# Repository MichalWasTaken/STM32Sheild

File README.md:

Shield for STM32 nucleo board to test nitrox analyzer project.

Components to be on the sield:
- Connectors
- Amplifier
- Button
- Potmeter
- Optional:
- Power elements (batt charger, buck-boost modules)

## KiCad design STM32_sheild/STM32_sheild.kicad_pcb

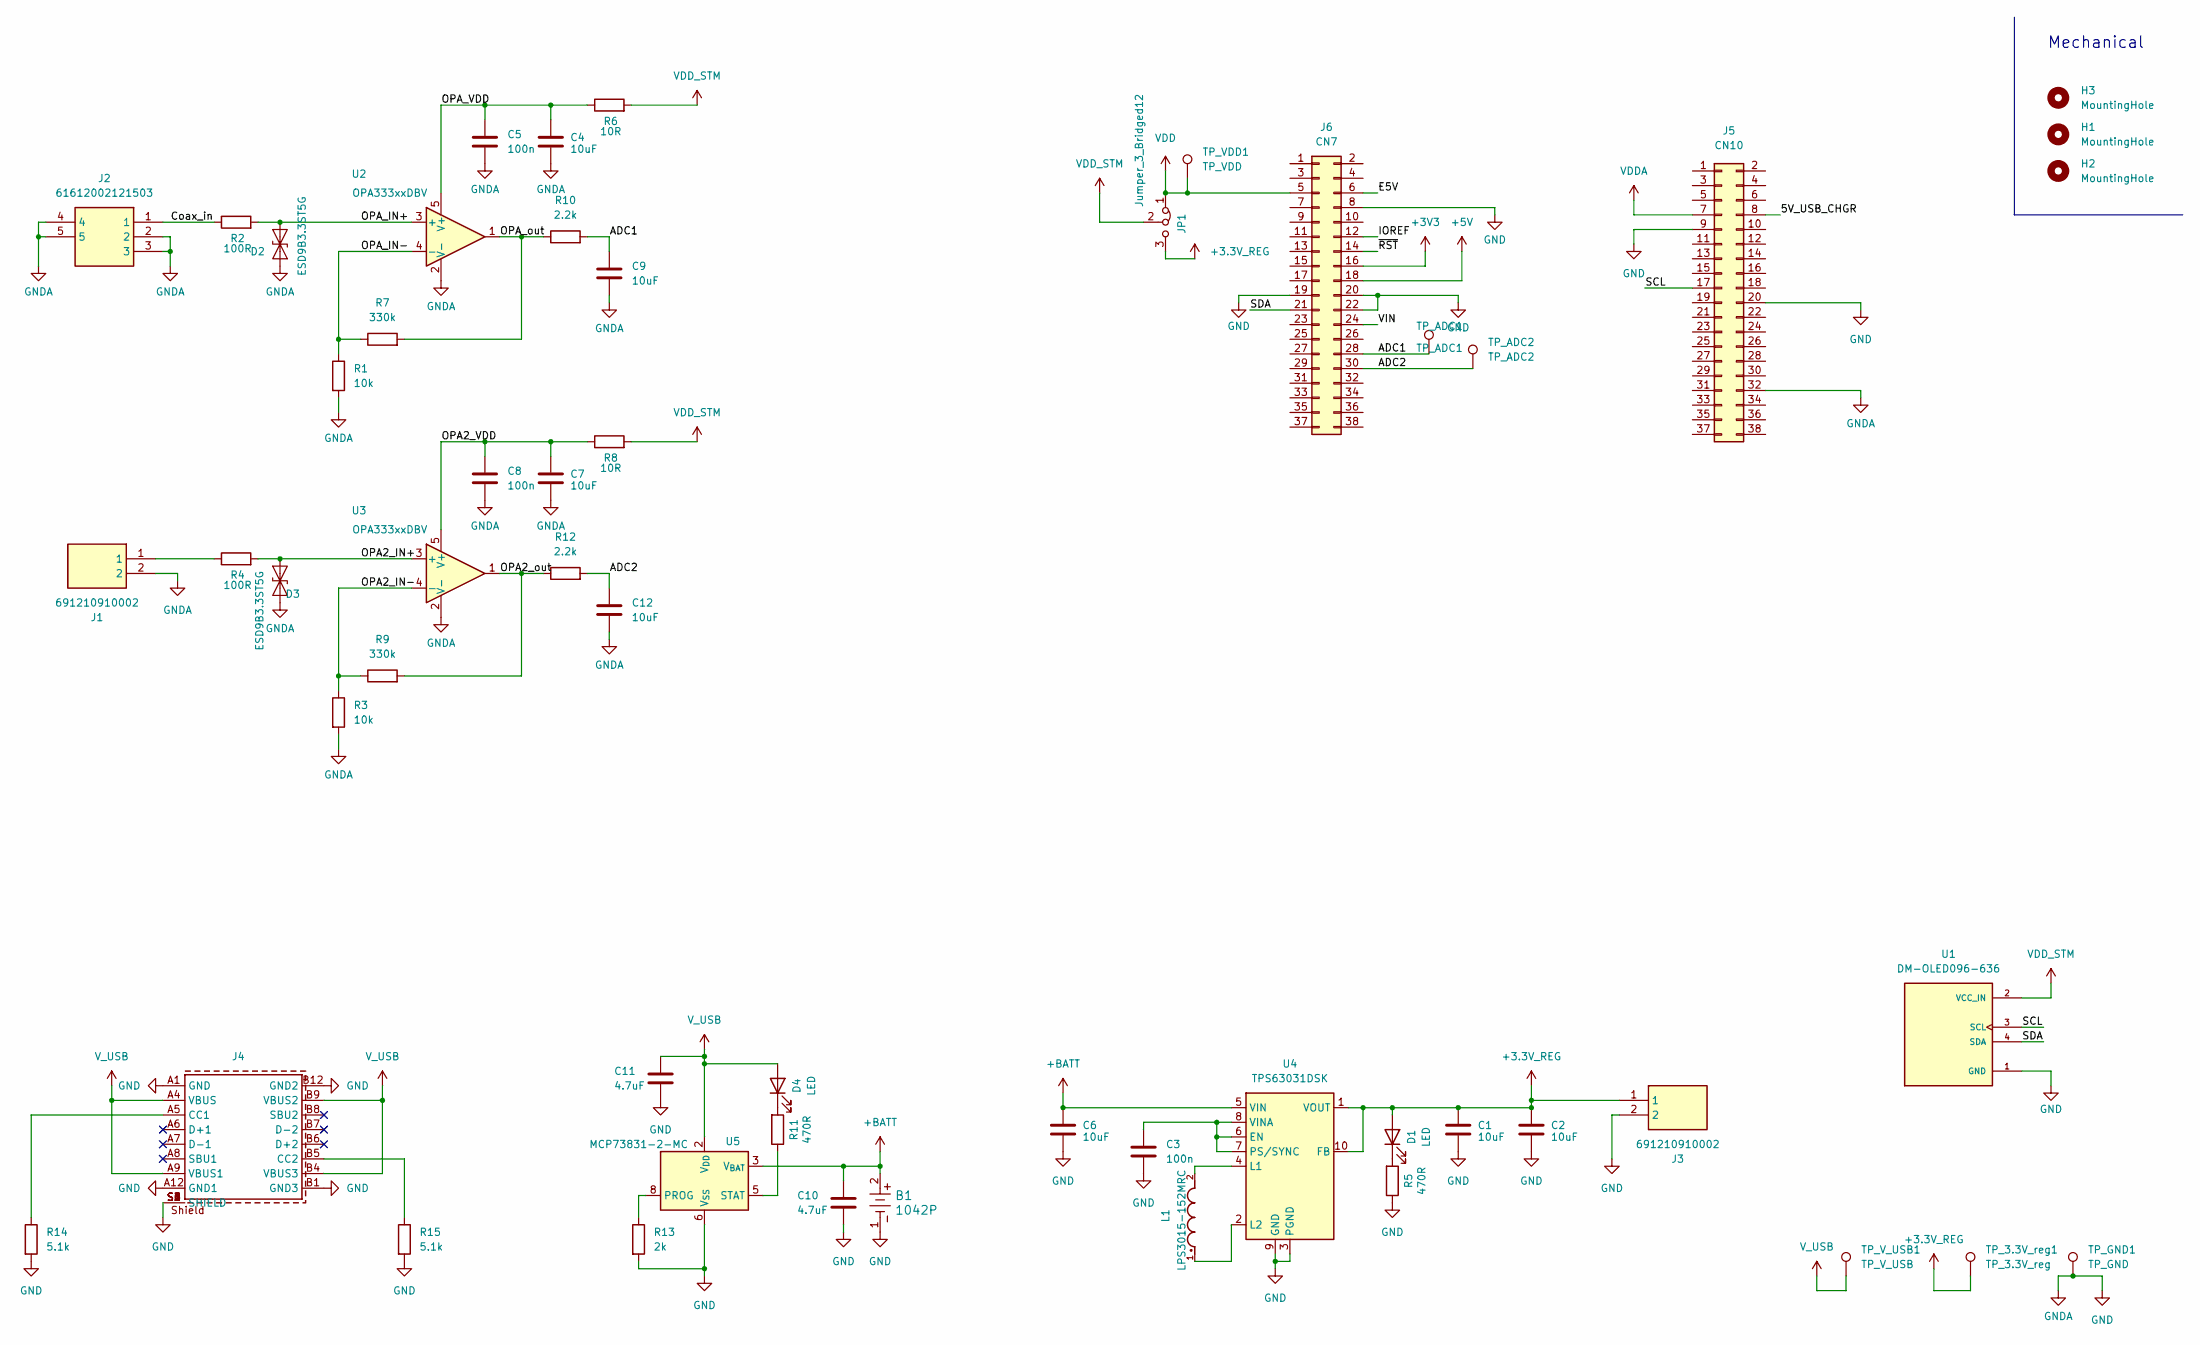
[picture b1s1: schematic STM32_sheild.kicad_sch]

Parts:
B1: 1042P; 1042P_KEY
C1, C2, C4, C6, C7, C9, C12: 10uF; C_0805_2012Metric
C3, C5, C8: 100n; C_0805_2012Metric
C10, C11: 4.7uF; C_0805_2012Metric
D1, D4: LED; LED_0805_2012Metric
D2, D3: ESD9B3.3ST5G; D_SOD-923
H1, H2, H3: MountingHole; MountingHole_3.2mm_M3
J1, J3: 691210910002; Mouser Part Number 710-691210910002
J2: 61612002121503; Mouser Part Number 710-61612002121503
J4: 629722010114; J_Wurth_WR-USB_629722050114; Working Voltage (V (DC)) 48 V (DC); Part Number 629722010114
J5: CN10; PinSocket_2x19_P2.54mm_Vertical
J6: CN7; PinSocket_2x19_P2.54mm_Vertical
JP1: Jumper_3_Bridged12; SolderJumper-3_P1.3mm_Bridged2Bar12_Pad1.0x1.5mm
L1: LPS3015-152MRC; IND_LPS3015-152MRC; PARTREV 12/13/21
R1, R3: 10k; R_0805_2012Metric
R2, R4: 100R; R_0805_2012Metric
R5, R11: 470R; R_0805_2012Metric
R6, R8: 10R; R_0805_2012Metric
R7, R9: 330k; R_0805_2012Metric
R10, R12: 2.2k; R_0805_2012Metric
R13: 2k; R_0805_2012Metric
R14, R15: 5.1k; R_0805_2012Metric
TP_3.3V_reg1: TP_3.3V_reg; TestPoint_Keystone_5010-5014_Multipurpose
TP_ADC1: TP_ADC1; TestPoint_Keystone_5010-5014_Multipurpose
TP_ADC2: TP_ADC2; TestPoint_Keystone_5010-5014_Multipurpose
TP_GND1: TP_GND; TestPoint_Keystone_5010-5014_Multipurpose
TP_VDD1: TP_VDD; TestPoint_Keystone_5010-5014_Multipurpose
TP_V_USB1: TP_V_USB; TestPoint_Keystone_5010-5014_Multipurpose
U1: DM-OLED096-636; MODULE_DM-OLED096-636; PARTREV 2018-09-10
U2, U3: OPA333xxDBV; SOT-23-5
U4: TPS63031DSK; WSON-10-1EP_2.5x2.5mm_P0.5mm_EP1.2x2mm
U5: MCP73831-2-MC; DFN-8-1EP_3x2mm_P0.5mm_EP1.7x1.4mm

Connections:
+3.3V_REG: C1.1, C2.1, D1.2 (A), J3.1, JP1.3 (B), TP_3.3V_reg1.1 (1_1), U4.1 (VOUT), U4.10 (FB)
+3V3: J6.16
+5V: J6.18
+BATT: B1.2, C6.1, C10.1, U4.5 (VIN), U5.3 (V_{BAT}), U5.4 (V_{BAT})
/5V_USB_CHGR: J5.8
/ADC1: C9.1, J6.28, R10.2, TP_ADC1.1 (1_1)
/ADC2: C12.1, J6.30, R12.2, TP_ADC2.1 (1_1)
/Coax_in: J2.1, R2.1
/E5V: J6.6
/IOREF: J6.12
/OPA2_IN+: D3.2 (A2), R4.2, U3.3 (+)
/OPA2_IN-: R3.1, R9.1, U3.4 (-)
/OPA2_VDD: C7.1, C8.1, R8.1, U3.5 (V+)
/OPA2_out: R9.2, R12.1, U3.1
/OPA_IN+: D2.2 (A2), R2.2, U2.3 (+)
/OPA_IN-: R1.1, R7.1, U2.4 (-)
/OPA_VDD: C4.1, C5.1, R6.1, U2.5 (V+)
/OPA_out: R7.2, R10.1, U2.1
/SCL: J5.17, U1.3 (SCL)
/SDA: J6.21, U1.4 (SDA)
/VIN: J6.24
/~RST: J6.14
GND: B1.1, C1.2, C2.2, C3.2, C4.2, C5.2, C6.2, C7.2, C8.2, C9.2, C10.2, C11.2, C12.2, D2.1 (A1), D3.1 (A1), J1.2, J2.2, J2.3, J2.4, J2.5, J3.2, J4.A1 (GND), J4.A12 (GND1), J4.B1 (GND3), J4.B12 (GND2), J4.S1 (SHIELD), J4.S2 (SHIELD), J4.S3 (SHIELD), J4.S4 (SHIELD), J4.S5 (SHIELD), J4.S6 (SHIELD), J5.9, J5.20, J5.32, J6.8, J6.19, J6.20, J6.22, R1.2, R3.2, R5.1, R13.2, R14.2, R15.2, TP_GND1.1 (1_1), U1.1 (GND), U2.2 (V-), U3.2 (V-), U4.3 (PGND), U4.9 (GND), U4.11 (PGND), U5.6 (V_{SS})
unnamed: D1.1 (K), R5.2
unnamed: D4.1 (K), R11.2
unnamed: J1.1, R4.1
unnamed: J4.A5 (CC1), R14.1
unnamed: J4.B5 (CC2), R15.1
unnamed: C3.1, U4.6 (EN), U4.7 (PS/SYNC), U4.8 (VINA)
unnamed: L1.2, U4.4 (L1)
unnamed: L1.1, U4.2 (L2)
unnamed: R13.1, U5.8 (PROG)
unnamed: R11.1, U5.5 (STAT)
VDD: J6.5, JP1.1 (A), TP_VDD1.1 (1_1)
VDDA: J5.7
VDD_STM: JP1.2 (C), R6.2, R8.2, U1.2 (VCC_IN)
V_USB: C11.1, D4.2 (A), J4.A4 (VBUS), J4.A9 (VBUS1), J4.B4 (VBUS3), J4.B9 (VBUS2), TP_V_USB1.1 (1_1), U5.1 (V_{DD}), U5.2 (V_{DD})

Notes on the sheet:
Mechanical

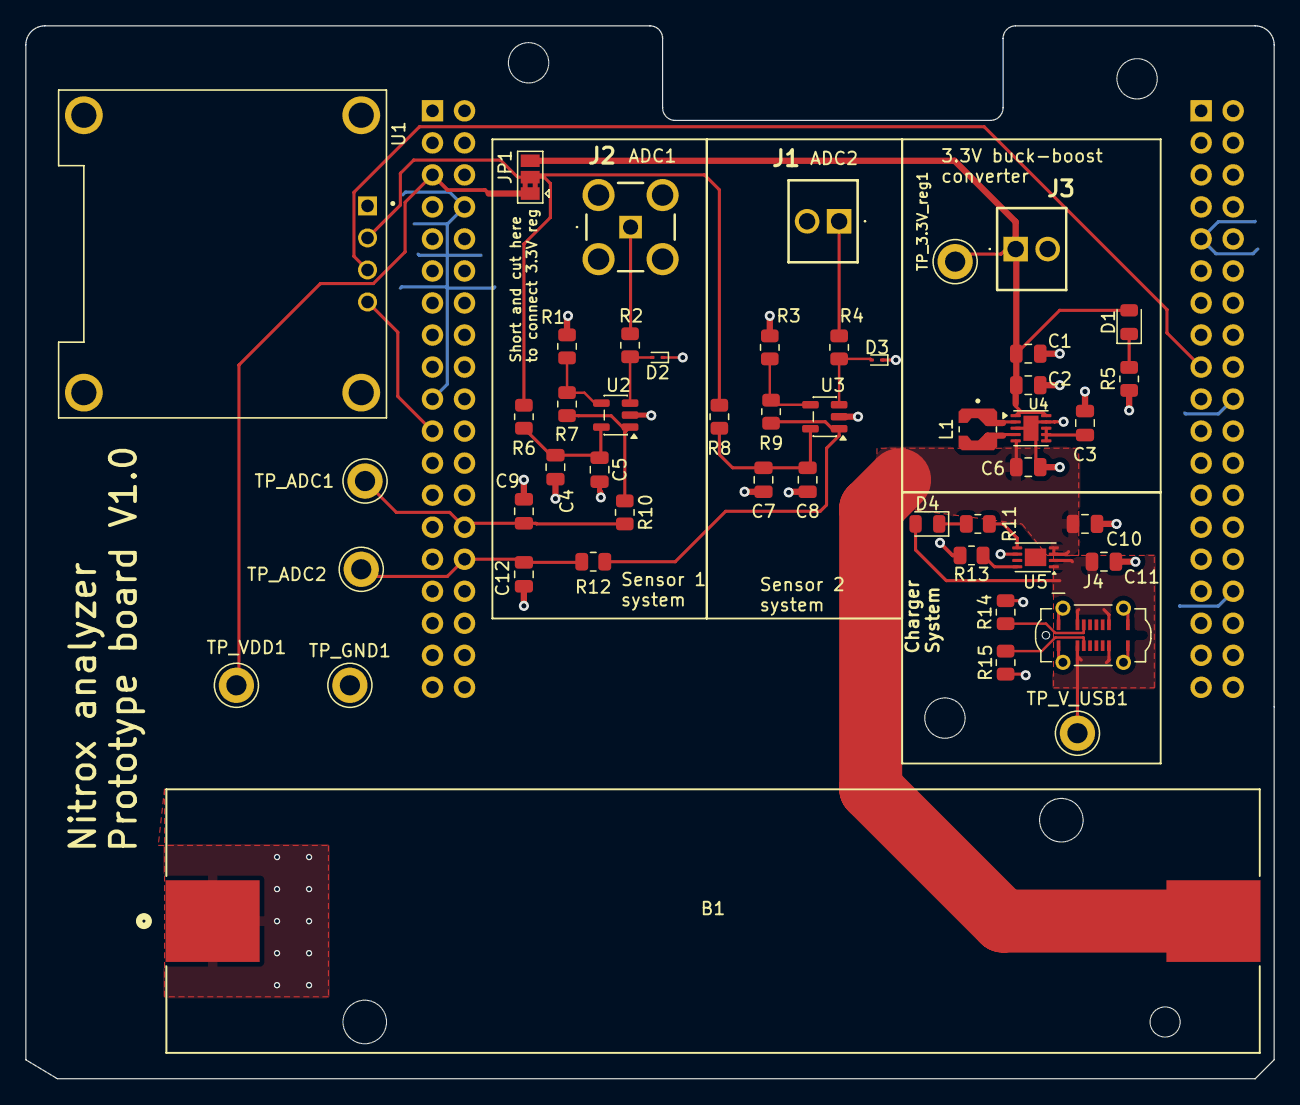
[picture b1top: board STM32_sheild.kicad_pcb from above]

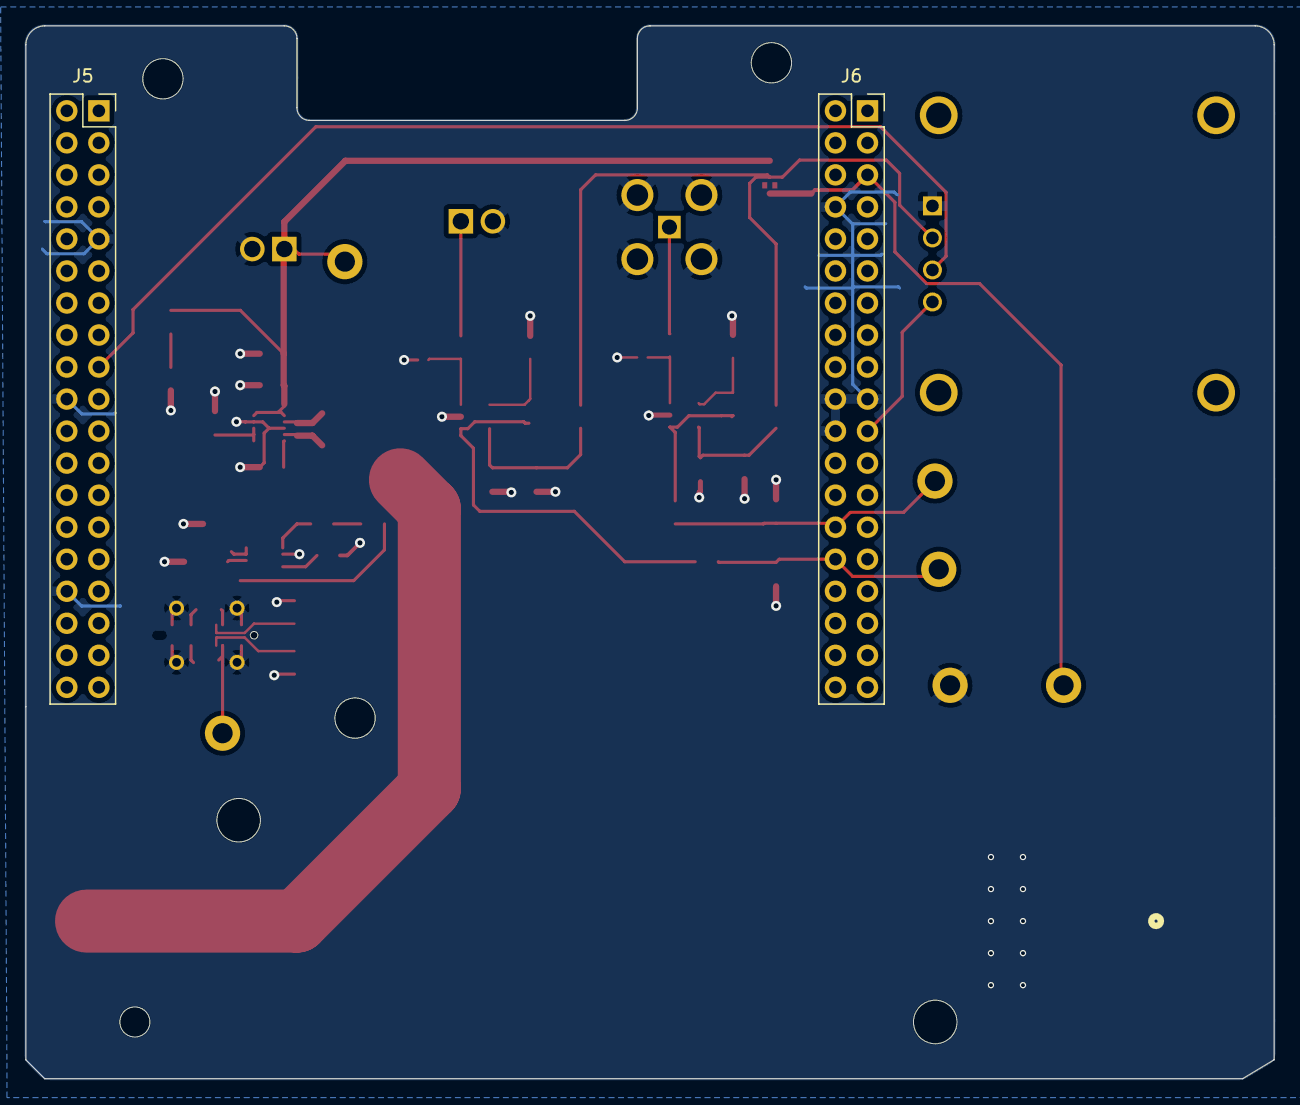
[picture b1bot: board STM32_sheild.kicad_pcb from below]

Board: 2 copper layers, 99.0 x 83.5 mm, 54 parts (2 on the bottom side), 29 nets.

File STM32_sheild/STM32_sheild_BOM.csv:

"Id;""Designator"";""Footprint"";""Quantity"";""Designation"";""Supplier and ref"";",,,,,,
"1;""B1"";""1042P_KEY"";1;""1042P"";;;",,,,,,
"2;""C1", C2, C4, C6, C7, C9," C12"";""C_0805_2012Metric"";7;""10uF"";;;"
"3;""C3", C5," C8"";""C_0805_2012Metric"";3;""100n"";;;",,,,
"4;""C10"," C11"";""C_0805_2012Metric"";2;""4.7uF"";;;",,,,,
"5;""D1"," D4"";""LED_0805_2012Metric"";2;""LED"";;;",,,,,
"6;""D2"," D3"";""D_SOD-923"";2;""ESD9B3.3ST5G"";;;",,,,,
"7;""H1", H2," H3"";""MountingHole_3.2mm_M3"";3;""MountingHole"";;;",,,,
"8;""J1"," J3"";""691210910002"";2;""691210910002"";;;",,,,,
"9;""J2"";""61612002121503"";1;""61612002121503"";;;",,,,,,
"10;""J4"";""J_Wurth_WR-USB_629722050114"";1;""629722010114"";;;",,,,,,
"11;""J5"";""PinSocket_2x19_P2.54mm_Vertical"";1;""CN10"";;;",,,,,,
"12;""J6"";""PinSocket_2x19_P2.54mm_Vertical"";1;""CN7"";;;",,,,,,
"13;""L1"";""IND_LPS3015-152MRC"";1;""LPS3015-152MRC"";;;",,,,,,
"14;""R1"," R3"";""R_0805_2012Metric"";2;""10k"";;;",,,,,
"15;""R2"," R4"";""R_0805_2012Metric"";2;""100R"";;;",,,,,
"16;""R5"," R11"";""R_0805_2012Metric"";2;""470R"";;;",,,,,
"17;""R6"," R8"";""R_0805_2012Metric"";2;""10R"";;;",,,,,
"18;""R7"," R9"";""R_0805_2012Metric"";2;""330k"";;;",,,,,
"19;""R10"," R12"";""R_0805_2012Metric"";2;""2.2k"";;;",,,,,
"20;""R13"";""R_0805_2012Metric"";1;""2k"";;;",,,,,,
"21;""R14"," R15"";""R_0805_2012Metric"";2;""5.1k"";;;",,,,,
"22;""TP_3.3V_reg1"";""TestPoint_Keystone_5010-5014_Multipurpose"";1;""TP_3.3V_reg"";;;",,,,,,
"23;""TP_ADC1"";""TestPoint_Keystone_5010-5014_Multipurpose"";1;""TP_ADC1"";;;",,,,,,
"24;""TP_ADC2"";""TestPoint_Keystone_5010-5014_Multipurpose"";1;""TP_ADC2"";;;",,,,,,
"25;""TP_GND1"";""TestPoint_Keystone_5010-5014_Multipurpose"";1;""TP_GND"";;;",,,,,,
"26;""TP_VDD1"";""TestPoint_Keystone_5010-5014_Multipurpose"";1;""TP_VDD"";;;",,,,,,
"27;""TP_V_USB1"";""TestPoint_Keystone_5010-5014_Multipurpose"";1;""TP_V_USB"";;;",,,,,,
"28;""U1"";""MODULE_DM-OLED096-636"";1;""DM-OLED096-636"";;;",,,,,,
"29;""U2"," U3"";""SOT-23-5"";2;""OPA333xxDBV"";;;",,,,,
"30;""U4"";""WSON-10-1EP_2.5x2.5mm_P0.5mm_EP1.2x2mm"";1;""TPS63031DSK"";;;",,,,,,
"31;""U5"";""DFN-8-1EP_3x2mm_P0.5mm_EP1.7x1.4mm"";1;""MCP73831-2-MC"";;;",,,,,,
